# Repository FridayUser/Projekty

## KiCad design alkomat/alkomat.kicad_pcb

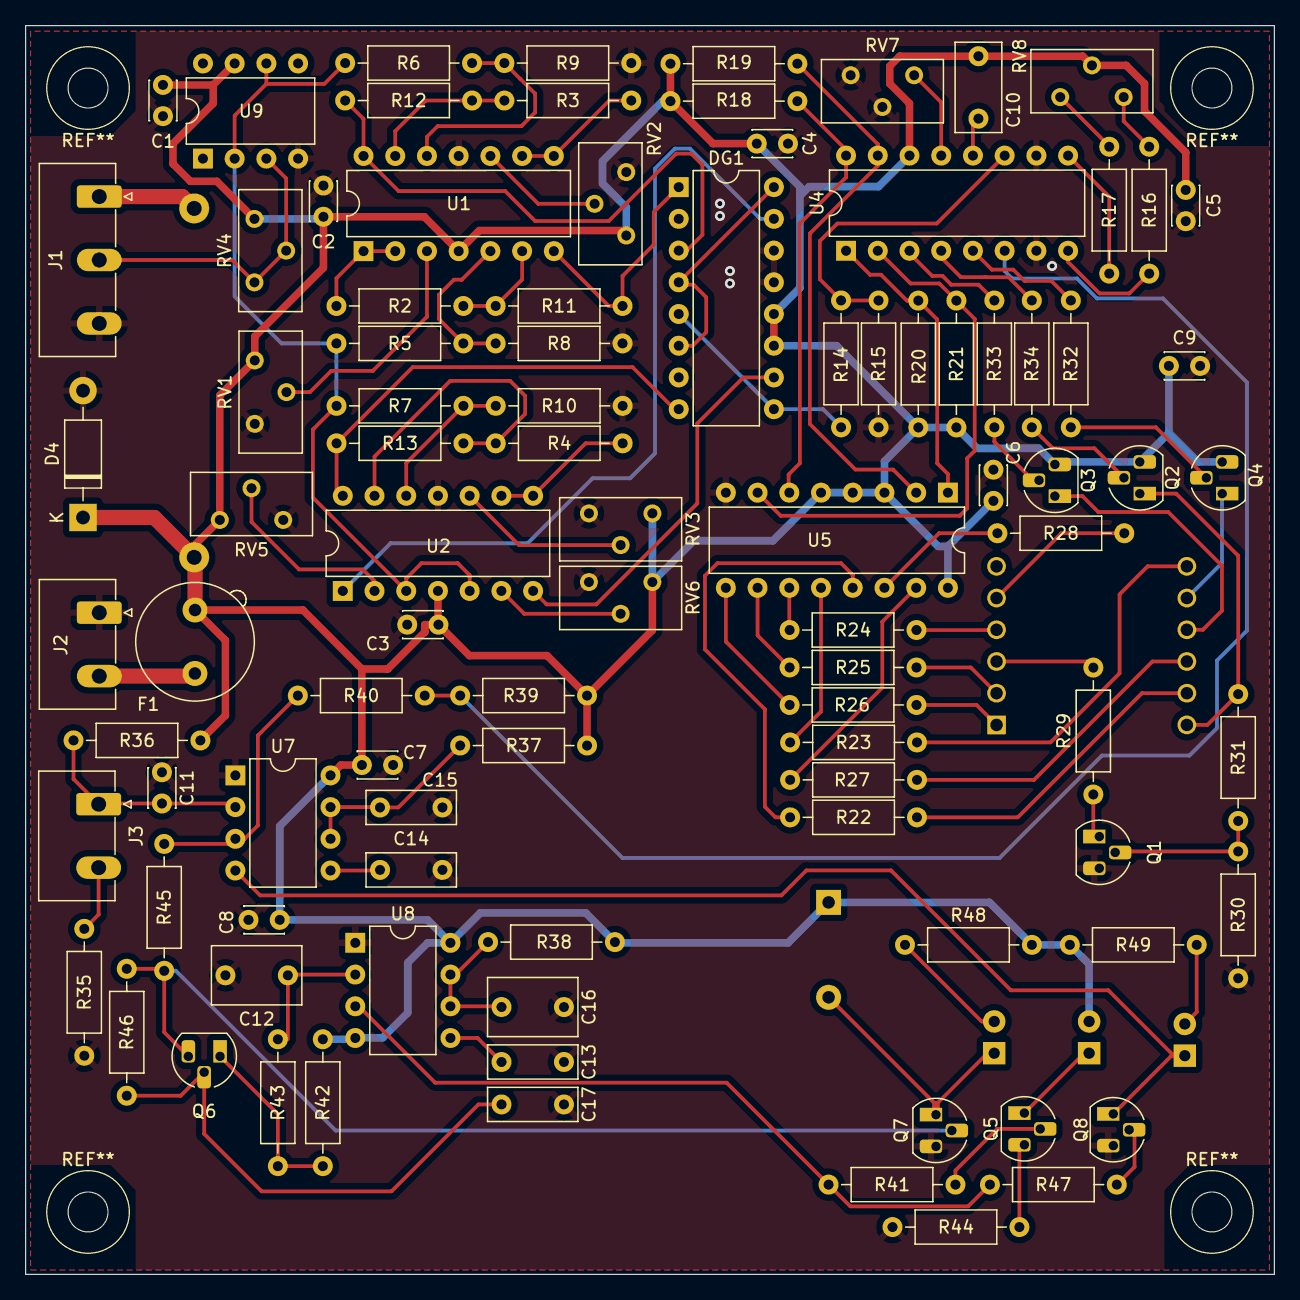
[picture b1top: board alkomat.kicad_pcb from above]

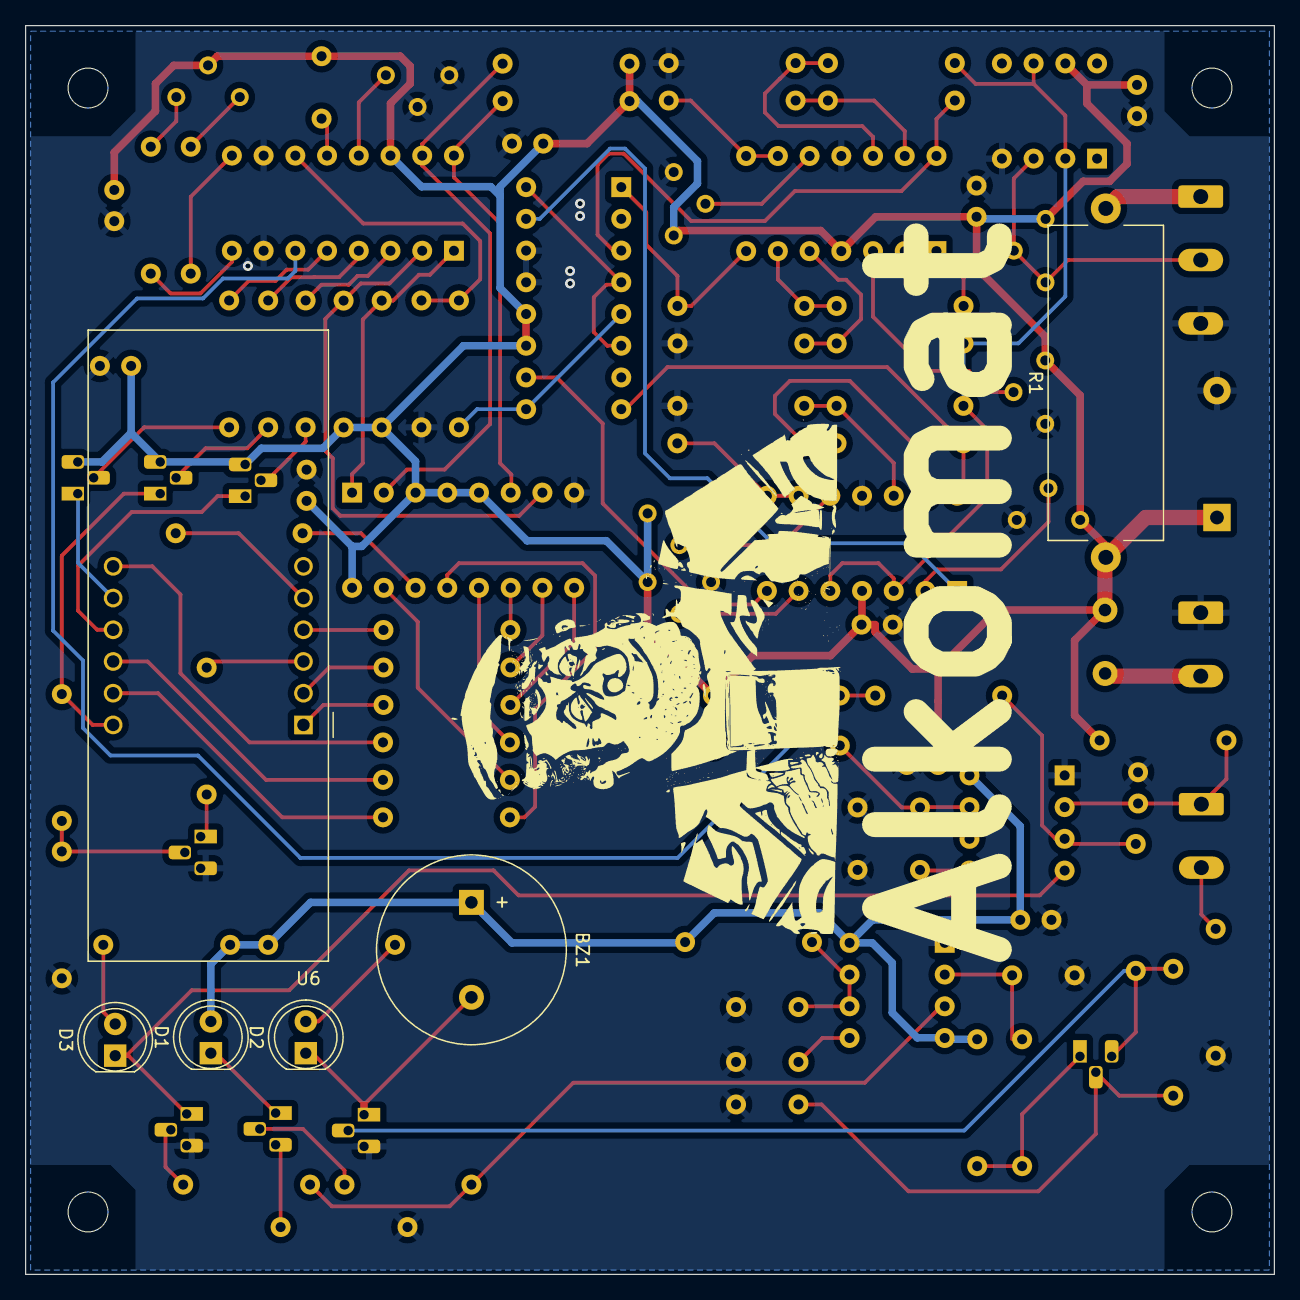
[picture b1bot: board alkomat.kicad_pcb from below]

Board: 2 copper layers, 100.0 x 100.0 mm, 100 parts (6 on the bottom side), 85 nets.

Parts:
BZ1: Buzzer; Buzzer_15x7.5RM7.6
C1, C2, C3, C4, C5, C6, C7, C8, C9, C11: 100n; C_Disc_D3.0mm_W2.0mm_P2.50mm
C10: 330n; C_Rect_L7.0mm_W3.5mm_P5.00mm
C12: 470n; C_Rect_L7.0mm_W4.5mm_P5.00mm
C13, C14: 10n; C_Rect_L7.0mm_W2.5mm_P5.00mm
C15: 100u; C_Rect_L7.0mm_W2.5mm_P5.00mm
C16: 470u; C_Rect_L7.0mm_W4.5mm_P5.00mm
C17: 100n; C_Rect_L7.0mm_W2.5mm_P5.00mm
D1: Green; LED_D5.0mm
D2: Blue; LED_D5.0mm
D3: Red; LED_D5.0mm
D4: 1N4007; D_DO-41_SOD81_P10.16mm_Horizontal
DG1: DIP-16_W7.62mm
F1: 1A; Fuseholder_TR5_Littelfuse_No560_No460
J1: Sensor input; ARK3
J2: Power_Input; ARK2
J3: button connector; ARK2
Q1, Q6, Q7, Q8: BC547; TO-92_HandSolder
Q2, Q3, Q4, Q5: BC557; TO-92_HandSolder
R1: 47; R_Axial_Power_L25.0mm_W9.0mm_P27.94mm
R2, R5, R9, R12: 56k; R_Axial_DIN0207_L6.3mm_D2.5mm_P10.16mm_Horizontal
R3, R6, R10, R13: 47k; R_Axial_DIN0207_L6.3mm_D2.5mm_P10.16mm_Horizontal
R4, R7, R18, R19, R20, R21, R36: 10k; R_Axial_DIN0207_L6.3mm_D2.5mm_P10.16mm_Horizontal
R8, R11, R39: 16k; R_Axial_DIN0207_L6.3mm_D2.5mm_P10.16mm_Horizontal
R14: 18k; R_Axial_DIN0207_L6.3mm_D2.5mm_P10.16mm_Horizontal
R15: 2k; R_Axial_DIN0207_L6.3mm_D2.5mm_P10.16mm_Horizontal
R16, R17: 20k; R_Axial_DIN0207_L6.3mm_D2.5mm_P10.16mm_Horizontal
R22, R23, R24, R25, R26, R27, R28, R29: 220; R_Axial_DIN0207_L6.3mm_D2.5mm_P10.16mm_Horizontal
R30, R35: 330; R_Axial_DIN0207_L6.3mm_D2.5mm_P10.16mm_Horizontal
R31, R32, R33, R34: 1k; R_Axial_DIN0207_L6.3mm_D2.5mm_P10.16mm_Horizontal
R37: 43k; R_Axial_DIN0207_L6.3mm_D2.5mm_P10.16mm_Horizontal
R38: 62k; R_Axial_DIN0207_L6.3mm_D2.5mm_P10.16mm_Horizontal
R40: 5.6k; R_Axial_DIN0207_L6.3mm_D2.5mm_P10.16mm_Horizontal
R41, R45, R47: 4.7k; R_Axial_DIN0207_L6.3mm_D2.5mm_P10.16mm_Horizontal
R42, R46: 100k; R_Axial_DIN0207_L6.3mm_D2.5mm_P10.16mm_Horizontal
R43: 47; R_Axial_DIN0207_L6.3mm_D2.5mm_P10.16mm_Horizontal
R44, R48, R49: 100; R_Axial_DIN0207_L6.3mm_D2.5mm_P10.16mm_Horizontal
RV1, RV2, RV3, RV5, RV6, RV8: 10k; Potentiometer_Bourns_3296Y_Vertical
RV4: 200k; Potentiometer_Bourns_3296Y_Vertical
RV7: 25k; Potentiometer_Bourns_3296Y_Vertical
U1, U2: MCP6004; DIP-14_W7.62mm
U4: C520D; DIP-16_W7.62mm
U5: 7447; DIP-16_W7.62mm
U6: LED-AT5636BMG; CA56-12EWA
U7, U8: NE555P; DIP-8_W7.62mm
U9: MCP601-xP; DIP-8_W7.62mm

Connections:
+5V: BZ1.1 (-), C1.1, C2.1, C3.1, C4.1, C5.1, C6.1, C7.1, C8.1, C9.1, C10.1, D1.2 (A), D4.1 (K), DG1.11 (V+), DG1.12 (VL), F1.2, Q2.3 (E), Q3.3 (E), Q4.3 (E), R1.1, R18.1, R19.1, R20.1, R21.1, R36.2, R37.2, R38.2, R39.2, R42.2, R48.2, R49.2, RV1.1, RV2.1, RV3.1, RV4.1, RV5.1, RV6.1, RV8.2, U1.4 (V+), U2.4 (V+), U4.14 (V+), U5.3 (~LT), U5.4 (~BI), U5.5 (~RBI), U5.16 (VCC), U7.8 (VCC), U8.4 (R), U8.8 (VCC), U9.7 (V+)
GND: C1.2, C2.2, C3.2, C4.2, C5.2, C6.2, C7.2, C8.2, C9.2, C11.2, C12.2, C13.2, C14.2, C15.2, C16.2, C17.2, D4.2 (A), DG1.13 (GND), DG1.14 (V-), J1.3, J2.1, Q1.3 (E), Q7.3 (E), Q8.3 (E), R8.2, R9.2, R10.2, R15.2, R30.1, R35.1, R44.1, RV1.3, RV2.3, RV3.3, RV5.3, RV6.3, RV7.2, RV7.3, U1.11 (V-), U2.11 (V-), U4.7 (GND), U4.10 (LOW_INPUT), U5.8 (GND), U7.1 (GND), U8.1 (GND), U9.4 (V-)
unnamed: BZ1.2 (+), D2.1 (K), Q7.1 (C)
unnamed: D1.1 (K), Q5.1 (C)
unnamed: D2.2 (A), R48.1
unnamed: D3.2 (A), R49.1
unnamed: DG1.4 (S3), DG1.6 (D4), DG1.16 (S1)
unnamed: DG1.15 (IN1), U2.1
unnamed: DG1.10 (IN2), U2.7
unnamed: J1.1, R1.2
unnamed: J1.2, RV4.2, RV4.3, U9.3 (+)
unnamed: F1.1, J2.2
unnamed: C11.1, J3.1, R36.1, U7.2 (TR)
unnamed: J3.2, R35.2
unnamed: Q1.2 (B), R30.2, R31.1
unnamed: Q1.1 (C), R29.1
unnamed: Q2.2 (B), R34.2
unnamed: Q2.1 (C), R31.2, U6.12 (CA_dig.1)
unnamed: Q3.2 (B), R33.2
unnamed: Q3.1 (C), U6.9 (CA_dig.2)
unnamed: Q4.2 (B), R32.2
unnamed: Q4.1 (C), U6.8 (CA_dig.3)
unnamed: Q5.2 (B), R41.1
unnamed: Q5.3 (E), R44.2
unnamed: C17.1, Q6.2 (B), R46.1
unnamed: Q6.1 (C), R42.1, R43.2
unnamed: Q6.3 (E), Q7.2 (B), R45.1, R46.2
unnamed: Q8.2 (B), R47.1
unnamed: R16.1, RV8.3
unnamed: R16.2, U4.8 (ZERO_ADJ)
unnamed: R17.1, RV8.1
unnamed: R17.2, U4.9 (ZERO_ADJ)
unnamed: RV1.2, U1.3 (+)
unnamed: R2.2, U1.1, U1.2 (-)
unnamed: R5.1, R8.1, U1.5 (+)
unnamed: R2.1, R11.2, U1.6 (-)
unnamed: RV2.2, U1.10 (+)
unnamed: R3.2, U1.8, U1.9 (-)
unnamed: R6.1, R9.1, U1.12 (+)
unnamed: R3.1, R12.2, U1.13 (-)
unnamed: RV5.2, U2.2 (-)
unnamed: RV6.2, U2.6 (-)
unnamed: RV3.2, U2.10 (+)
unnamed: R4.2, U2.8, U2.9 (-)
unnamed: R7.1, R10.1, U2.12 (+)
unnamed: R4.1, R13.2, U2.13 (-)
unnamed: RV7.1, U4.13 (GAIN_ADJ)
unnamed: R14.1, R15.1, U4.11 (HIGH_INPUT)
unnamed: C10.2, U4.12 (INTEGR_CAP)
unnamed: R32.1, U4.5 (LSD)
unnamed: R34.1, U4.4 (MSD)
unnamed: R33.1, U4.3 (NSD)
unnamed: R21.2, U4.2 (Q_{A}), U5.7 (A)
unnamed: R20.2, U4.1 (Q_{B}), U5.1 (B)
unnamed: R19.2, U4.15 (Q_{C}), U5.2 (C)
unnamed: R18.2, U4.16 (Q_{D}), U5.6 (D)
unnamed: R22.1, U5.13 (~a)
unnamed: R23.1, U5.12 (~b)
unnamed: R24.1, U5.11 (~c)
unnamed: R25.1, U5.10 (~d)
unnamed: R26.1, U5.9 (~e)
unnamed: R27.1, U5.15 (~f)
unnamed: R28.1, U5.14 (~g)
unnamed: R22.2, U6.11 (A)
unnamed: R23.2, U6.7 (B)
unnamed: R24.2, U6.4 (C)
unnamed: R25.2, U6.2 (D)
unnamed: R29.2, U6.3 (DP)
unnamed: R26.2, U6.1 (E)
unnamed: R27.2, U6.10 (F)
unnamed: R28.2, U6.5 (G)
unnamed: C14.1, U7.5 (CV)
unnamed: C15.1, R37.1, U7.6 (THR), U7.7 (DIS)
unnamed: R40.1, R45.2, U7.3 (Q)
unnamed: C13.1, U8.5 (CV)
unnamed: C16.1, R38.1, U8.6 (THR), U8.7 (DIS)
unnamed: R41.2, R47.2, U8.3 (Q)
final signal: DG1.5 (S4), DG1.9 (S2), R14.2
hold: R39.1, R40.2, U4.6 (HOLD/BYPAS)
reset: D3.1 (K), Q8.1 (C), U7.4 (R)
signal: R5.2, R6.2, R7.2, U2.3 (+), U2.5 (+), U9.2 (-), U9.6
signal 1: DG1.1 (D1), R11.1, U1.7
signal 2: DG1.3 (D3), R12.1, U1.14
signal 3: DG1.8 (D2), R13.1, U2.14
triger: C12.1, R43.1, U8.2 (TR)

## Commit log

2024-04-05 Alkomat
2024-04-05 Sorter
2024-04-05 film
